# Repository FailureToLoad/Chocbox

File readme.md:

# Chocbox

The objective of this project was to create a stickless controller with a low height body. To achieve this I swapped from standard buttons to instead using a PCB housing choc switches and 3d printed buttons designed to slot into them.

I chose choc switches since their design holds a 3d printed button much more securely than an mx switch while also being easier to print.

Refer to the [OnShape project](https://cad.onshape.com/documents/75e113c9407cf422c65e0889/v/74a9f620865811870f0dd645/e/7d5beb43c80cf76b58155f77?renderMode=0&uiState=647fb75370b34f6be44eeb65) to see what assembly roughly looks like. Please feel free to clone the project and change it however it suits you.

[The buttons were also designed in OnShape](https://cad.onshape.com/documents/3c28af6b43d2c4966163a2e3/w/c3540472dc935fdd22f11141/e/71cabcc9b349a1862c93366c?renderMode=0&uiState=64277b5fd101cb2a61f906aa). Same thing, please clone it and change it to suit your needs.

The drawings I used to order the top and bottom plate are in the drawings directory. I recommend SendCutSend if you choose to order your own. They work fast and their prices are reasonable for what you get.

The kicad projects that define the PCBs are in the PCB directory. Please try not to judge too harshly, I'm an amateur at best when it comes to PCB design. For anyone that wants to learn, the [PCB Design Guide by AI03](https://wiki.ai03.com/books/pcb-design/page/pcb-guide-part-1---preparations) is a great resource for the basics. The produced gerbers are also housed with each board's project. JLPCB is a great service to order these from.

Feel free to raise an issue through the repo for any questions/concerns.

## Construction
First and foremost the most important thing is a Brook fighting board. I used a UFB for this but you can cut costs by working out which system you'll play on primarily and getting that instead. The UFB works on all of them. You can absolutely use whatever main board you like, this project is more concered with keeping all the right parts secured in the right spots than it is specifically designed for a Brook board.  
[Brook UFB](https://www.amazon.com/Universal-Fighting-Compatible-preinstalled-Android-iOS/dp/B08H1TCFB1)

I used heat-set brass inserts on the mid section pieces since I 3d printed them. If you're using wood you can probably get just using wood screws or using a tap to thread the hole.  
[8x M3x4x5 heat-set inserts](https://dfh.fm/products/black-nickel-coated-threaded-heat-set-inserts?variant=43580471673054)  

For securing the plates to the mid section, the screws should be at least 6mm long. I only say this because the screws I used were 6mm, you could easily go longer so long as they aren't hitting each other in the hole.  
[8x at least 6mm M3](https://www.mcmaster.com/91294A126/)  

Securing the PCBs to the top plate was tricky. On the first of these I built, I was able to drill the holes fairly well so there was no evidence on the face. The second one... not so much. It helps to have a stop collar for your particular bit. Set the collar at about ~3-4 mm to start and be very careful. Additionally you could order a thicker top plate to help alleviate the issue. The answer to "well why didn't you?" is "I'm not smart".  

For the face button and cardinal PCBs use M3s to secure them.  
[12x 5mm M3](https://www.mcmaster.com/92005A114/)  

For the 6x6x5 PCBs, use M2s to secure them.  
[8x 5mm M2](https://www.mcmaster.com/92005A019/)  

The boards for the main buttons and cardinals use 2.54mm pitch connectors. Screw terminals are great as are JST connectors. I went with screw terminals since crimping wire connectors can be a bit frustrating sometimes.  
[3x 5 position 2.54 mm pitch screw terminals](https://www.digikey.com/en/products/detail/w%C3%BCrth-elektronik/691210910005/11477521)  

The small boards for the control buttons and L3/R3 use 2mm pitch connectors. I designed them with JST-PH connectors in mind. If you don't have crimpers and don't want to buy them just for this project, its totally valid to just solder the wires directly to the board. The following are link is for a connector kit since its kind of annoying to order all the bits of the connector assembly separate. For the crimpers, most crimping pliers on amazon will do the trick. Just make sure the pliers can handle 1.6 and 1.9 mm widths. Also, don't go nuts on a pair of strippers. I personally have a pair of [these](https://www.amazon.com/Stripper-Stranded-Klein-Tools-1003/dp/B000V6W5QU/ref=sr_1_59?crid=3C40FWK0G2Q9M&keywords=wire+strippers&qid=1686095615&sprefix=wire+strippers%2Caps%2C160&sr=8-59) and they're fine  
[2x 4 pos 2mm pitch JST-PH connectors](https://www.amazon.com/CQRobot-Connector-Terminal-Industrial-Integrated/dp/B0731MZCGF)    

For the 6x6x5 buttons, focus more on the 6x6 length x width than the 5mm height. [Packs of buttons](https://www.amazon.com/gp/product/B07C7211PJ/ref=ppx_yo_dt_b_search_asin_image?ie=UTF8&psc=1) can be gotten on amazon for a fair price but they can also be ordered individually from Digikey or McMaster Carr.   
[6x 6x6x5 momentary push-button switches (McMaster)](https://www.mcmaster.com/1821N11/)   

Digikey can be a bit overwhelming, hopefully [this link](https://www.digikey.com/en/products/filter/tactile-switches/197?s=N4IgjCBcpgzADFUBjKAzAhgGwM4FMAaEAeygG0QAWeANhtpAF0iAHAFyhAGU2AnASwB2AcxABfIgFYaAdiQhUkTLkIlyIAEyT4kmQA4mrDpG58hoiSAC0G%2BYr4BXVaUgVJTMZ6A) goes right to the search I used. In the Switches -> Tactile Switch section, use the search to set the Circuit to SPST-NO and the Outline to 6.0mm x 6.0mm   

This is the *exact* part I ordered and the board's tolerances were designed specifically for it.  
[USB Type B male to type B female extension](https://www.amazon.com/gp/product/B00S5WJ5RO/ref=ppx_yo_dt_b_search_asin_title?ie=UTF8&psc=1)  

Dealer's choice on which flavor of choc switch to go with, I suggest staying in the 30-50gf range for actuation force.   
[12x kailh choc keyswitches](https://mkultra.click/choc-switches)   

This is the exact cable I use but honestly, any B to A cable will do fine.   
[Amazon Basics 6ft USB-A to USB-B cable](https://www.amazon.com/Amazon-Basics-External-Gold-Plated-Connectors/dp/B00NH11KIK/ref=sr_1_2?crid=8LI8RN92O9J4&keywords=Amazon%2BBasics%2BUSB-A%2Bto%2BUSB-B%2B2.0&qid=1686093715&s=electronics&sprefix=amazon%2Bbasics%2Busb-a%2Bto%2Busb-b%2B2.0%2B%2Celectronics%2C111&sr=1-2&th=1)   

For wiring between components I use ~22-24AWG wire. I generally go with PVC coated instead of silicone since its easier to get it to sit still. If you plan on being fancy and crimping ferrules onto your wire ends, I'd suggest going with 22 AWG since its easier to find ferrules for that gauge.    
[24 AWG Hookup Wire](https://www.amazon.com/gp/product/B073QHPGMC/ref=ppx_yo_dt_b_search_asin_title?ie=UTF8&th=1)  

## Total Parts List
The parts listed here are mainly for reference and comparison so you can source your parts through a supplier that's more economically sound for you. The sources I list are mainly American suppliers so for anyone outside the continental US, shipping might make them insane choices.  

[1x PCB](https://www.amazon.com/Universal-Fighting-Compatible-preinstalled-Android-iOS/dp/B08H1TCFB1)  
[8x M3x4x5 heat-set inserts](https://dfh.fm/products/black-nickel-coated-threaded-heat-set-inserts?variant=43580471673054)   
[8x ~6mm M3](https://www.mcmaster.com/91294A126/)  
[12x 5mm M3](https://www.mcmaster.com/92005A114/)  
[8x 5mm M2](https://www.mcmaster.com/92005A019/)  
[3x 5 position 2.54 mm pitch screw terminals](https://www.digikey.com/en/products/detail/w%C3%BCrth-elektronik/691210910005/11477521)  
[2x 4 pos 2mm pitch JST-PH connectors](https://www.amazon.com/CQRobot-Connector-Terminal-Industrial-Integrated/dp/B0731MZCGF)  
[6x 6x6x5 momentary push-button switches](https://www.mcmaster.com/1821N11/)  
[1x USB Type B male to type B female extension](https://www.amazon.com/gp/product/B00S5WJ5RO/ref=ppx_yo_dt_b_search_asin_title?ie=UTF8&psc=1)  
[12x kailh choc keyswitches](https://mkultra.click/choc-switches)  
[1x USB-A to USB-B cable](https://www.amazon.com/Amazon-Basics-External-Gold-Plated-Connectors/dp/B00NH11KIK/ref=sr_1_2?crid=8LI8RN92O9J4&keywords=Amazon%2BBasics%2BUSB-A%2Bto%2BUSB-B%2B2.0&qid=1686093715&s=electronics&sprefix=amazon%2Bbasics%2Busb-a%2Bto%2Busb-b%2B2.0%2B%2Celectronics%2C111&sr=1-2&th=1)  
[Hookup wire](https://www.amazon.com/gp/product/B073QHPGMC/ref=ppx_yo_dt_b_search_asin_title?ie=UTF8&th=1)  

## Credit

[6x6x5 pushbutton step file](https://www.mcmaster.com/1821N11/)  
[4pos terminal connector step file](https://www.phoenixcontact.com/en-us/products/printed-circuit-board-terminal-mpt-05-5-254-1725685)  
[Kailh choc switch step file](https://grabcad.com/library/kailh-choc-low-profile-switch-1)  
[USB Type B panel mount step file](https://grabcad.com/library/usb-type-b-panel-mount-1)  
[Kailh choc 1u keycap](https://grabcad.com/library/kailh-lp-choc-keycap-for-corne-1)

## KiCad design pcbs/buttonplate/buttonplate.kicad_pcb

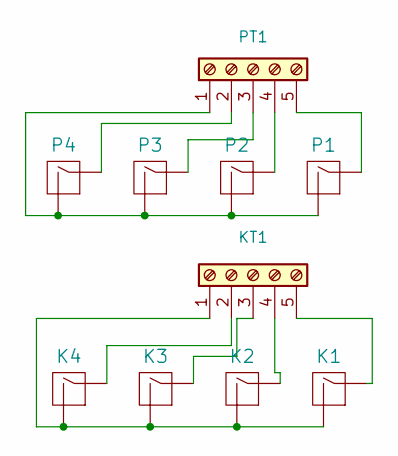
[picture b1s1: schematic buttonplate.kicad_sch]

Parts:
K1, K2, K3, K4: MX-1U; mx-1350-hybrid
KT1: Screw_Terminal_01x05; TerminalBlock_Phoenix_MPT-0,5-5-2.54_1x05_P2.54mm_Horizontal
P1, P2, P3, P4: MX-1U; mx-1350-hybrid
PT1: Screw_Terminal_01x05; TerminalBlock_Phoenix_MPT-0,5-5-2.54_1x05_P2.54mm_Horizontal

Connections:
unnamed: K1.1 (COL), KT1.5
unnamed: K1.2 (ROW), K2.2 (ROW), K3.2 (ROW), K4.2 (ROW), KT1.1
unnamed: K2.1 (COL), KT1.4
unnamed: K3.1 (COL), KT1.3
unnamed: K4.1 (COL), KT1.2
unnamed: P1.1 (COL), PT1.5
unnamed: P1.2 (ROW), P2.2 (ROW), P3.2 (ROW), P4.2 (ROW), PT1.1
unnamed: P2.1 (COL), PT1.4
unnamed: P3.1 (COL), PT1.3
unnamed: P4.1 (COL), PT1.2

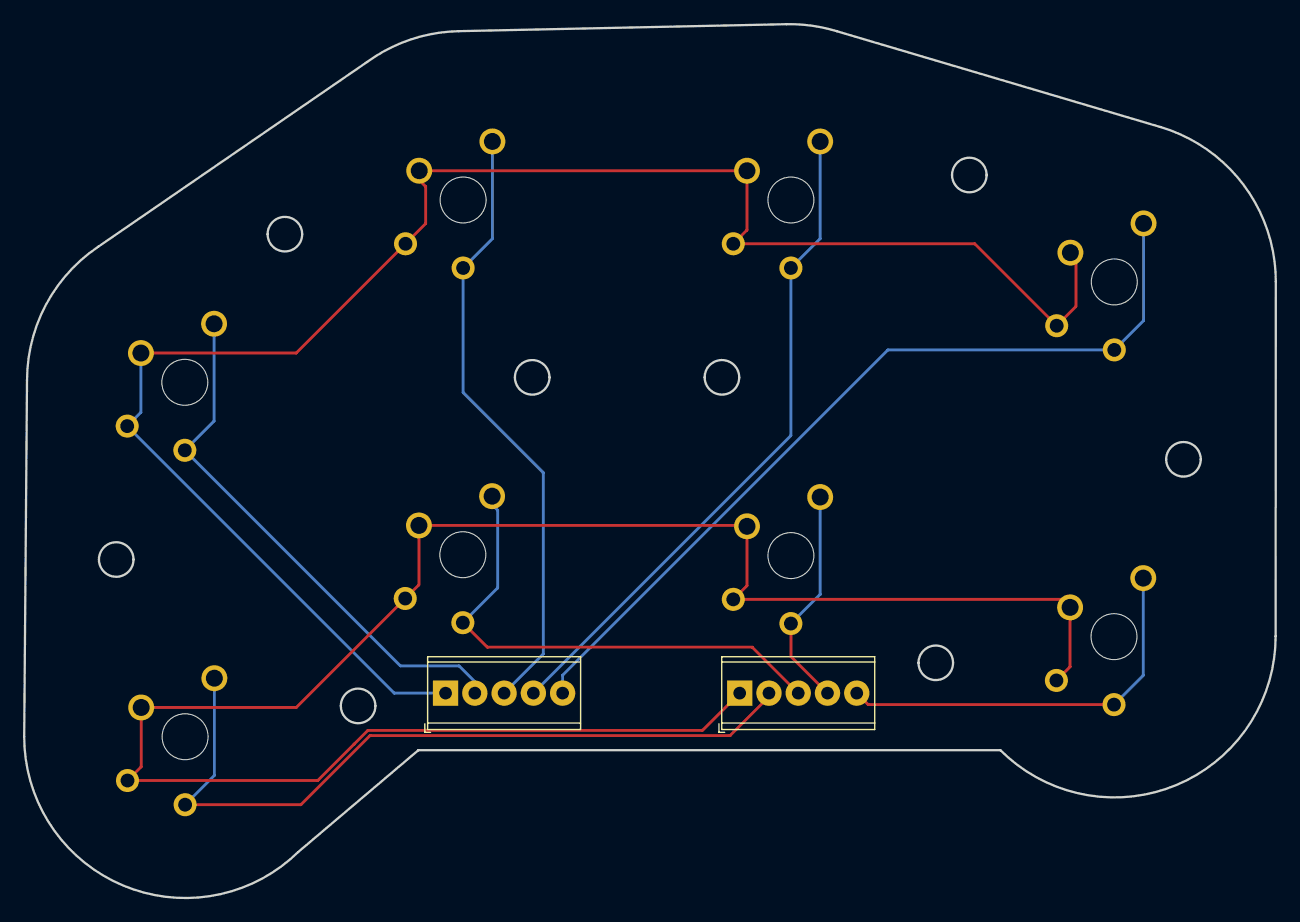
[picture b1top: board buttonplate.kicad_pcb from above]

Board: 2 copper layers, 108.6 x 75.8 mm, 10 parts (0 on the bottom side), 10 nets.

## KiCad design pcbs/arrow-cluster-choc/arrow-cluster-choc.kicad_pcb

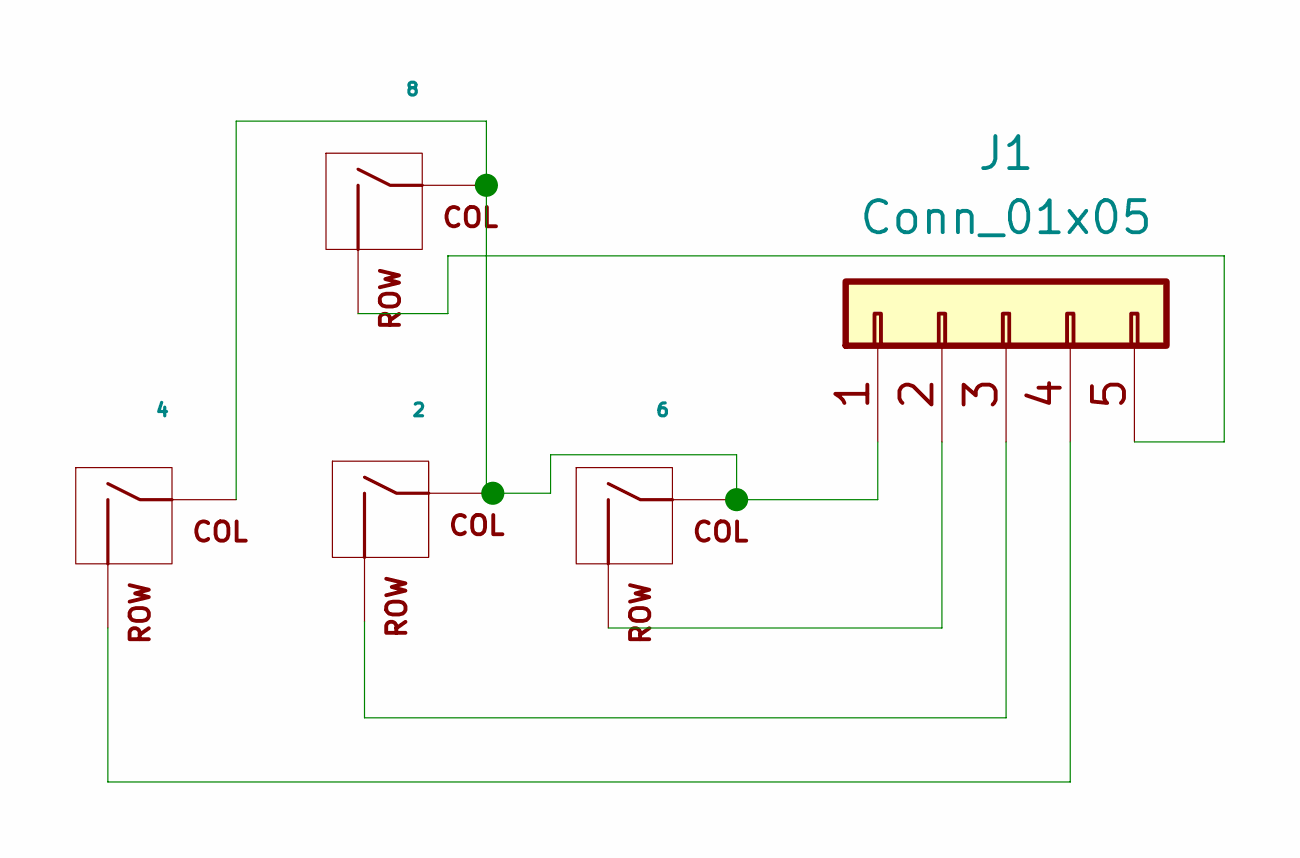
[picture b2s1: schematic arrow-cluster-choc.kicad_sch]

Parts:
J1: Conn_01x05; PinSocket_1x05_P2.54mm_Vertical
MX1: 4; KailhChoc-1U
MX2: 8; KailhChoc-1U
MX3: 2; KailhChoc-1U
MX4: 6; KailhChoc-1U

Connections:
unnamed: J1.1, MX1.1 (COL), MX2.1 (COL), MX3.1 (COL), MX4.1 (COL)
unnamed: J1.2, MX4.2 (ROW)
unnamed: J1.3, MX3.2 (ROW)
unnamed: J1.4, MX1.2 (ROW)
unnamed: J1.5, MX2.2 (ROW)

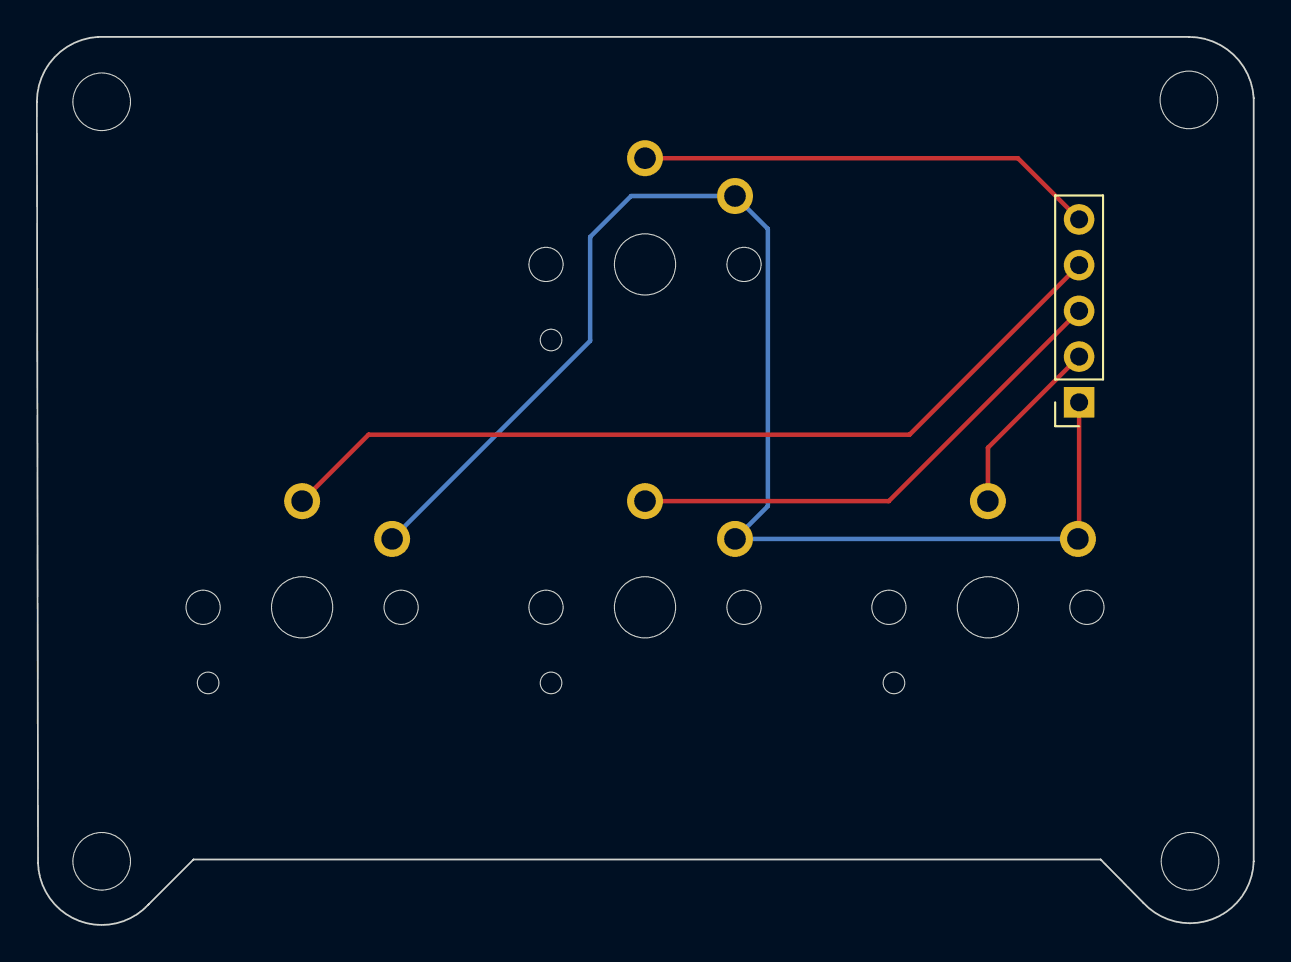
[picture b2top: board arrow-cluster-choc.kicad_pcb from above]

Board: 2 copper layers, 67.6 x 49.3 mm, 5 parts (0 on the bottom side), 5 nets.

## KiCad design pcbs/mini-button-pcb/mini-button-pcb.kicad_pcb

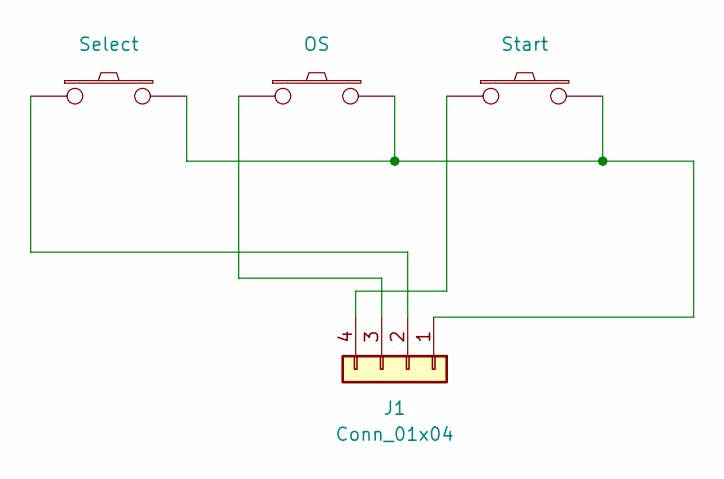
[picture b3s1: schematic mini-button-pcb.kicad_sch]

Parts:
J1: Conn_01x04; JST_PH_S4B-PH-K_1x04_P2.00mm_Horizontal
SW1: Select; SW_PUSH_6mm_H5mm
SW2: OS; SW_PUSH_6mm_H5mm
SW3: Start; SW_PUSH_6mm_H5mm

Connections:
unnamed: J1.1, SW1.2, SW2.2, SW3.2
unnamed: J1.2, SW1.1
unnamed: J1.3, SW2.1
unnamed: J1.4, SW3.1

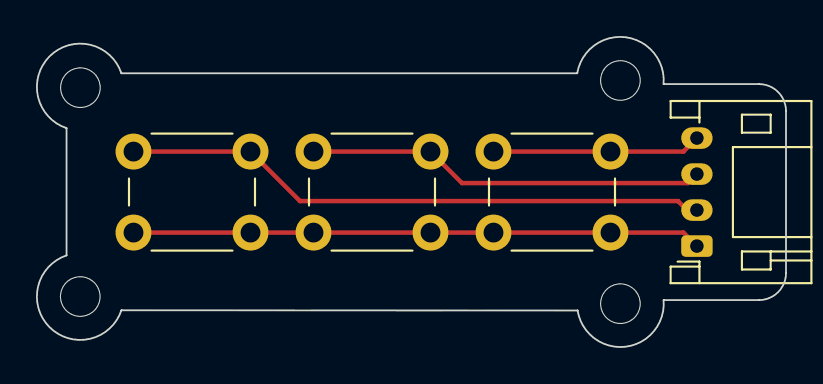
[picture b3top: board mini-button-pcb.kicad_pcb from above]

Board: 2 copper layers, 41.6 x 17.2 mm, 4 parts (0 on the bottom side), 4 nets.

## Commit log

2023-04-01 adds initial files
2023-06-07 updates readme with details on parts
2023-06-07 fixes formatting on parts list
2023-06-07 adds MIT license
